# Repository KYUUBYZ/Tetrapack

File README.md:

# Tetrapack

<!--START_SECTION:BOM-TABLE-->
| Item | Qty | Supplier | Cost/item | Total Cost | link |
| --- | --- | --- | --- | --- | --- |
| Keyboard switches | 10 | Amazon | $7.28 | $7.28 | [Link](https://amzn.eu/d/03ocpfXx) |
| 20mm Plum handle | 1 | Aliexpress | $3.18 | $3.18 | [Link](https://it.aliexpress.com/item/1005009018396383.html?spm=a2g0o.detail.0.0.4a692ax52ax5IX&mp=1&pdp_npi=6%40dis%21EUR%21EUR+1.85%21EUR+1.85%21%21EUR+1.85%21%21%21%400b884b5817914834751998203e0efd%2112000047696154340%21ct%21IT%216215000935%21%212%210%21&_gl=1*12osb1n*_gcl_aw*R0NMLjE3OTA4ODQwMTEuQ2p3S0NBandpZmpWQmhCS0Vpd0FZeDRLOUV2cDdHVGR4MzdlMFFod2J2MVQyLXlndkJxdTJrSXZ4cHBPYnp2YVp2Y3BiVGtESldkVkJob0NEeDRRQXZEX0J3RQ..*_gcl_au*NzAxNTU5NzE5LjE3OTA4NzM0MTQ.*_ga*MjEzNDk1ODc5NjA4MTA1MC4xNzkwODczNDEzNDAz*_ga_VED1YSGNC7*czE3OTE0ODMzOTAkbzE5JGcxJHQxNzkxNDgzNDU1JGo2MCRsMCRoMA..&gatewayAdapt=glo2ita) |
| Display OLED 0,91 | 1 | Amazon | $9.98 | $9.98 | [Link](https://amzn.eu/d/0f2XTxEG) |
| Rp 2040 Zero | 1 | Amazon | $9.98 | $9.98 | [Link](https://amzn.eu/d/0fHYzSj0) |
| Estimated total shipping | 1 |  |  | $3 |  |
<!--END_SECTION:BOM-TABLE-->

TETRAPACK is a 9 keys, high pulling rate macropad, it exists because people (like me) needs shortcuts to things like programs, aps or maybe even channels on discord, or just use it for geometry dash (what I will do) or OSU.

The simbols schematic:

The PCB schematic:

It's a high pulling rate (1000hz) macropad, it's this fast because it uses a certain USB-c propriety useful for projects like this, everything about it (the code) is in src/host

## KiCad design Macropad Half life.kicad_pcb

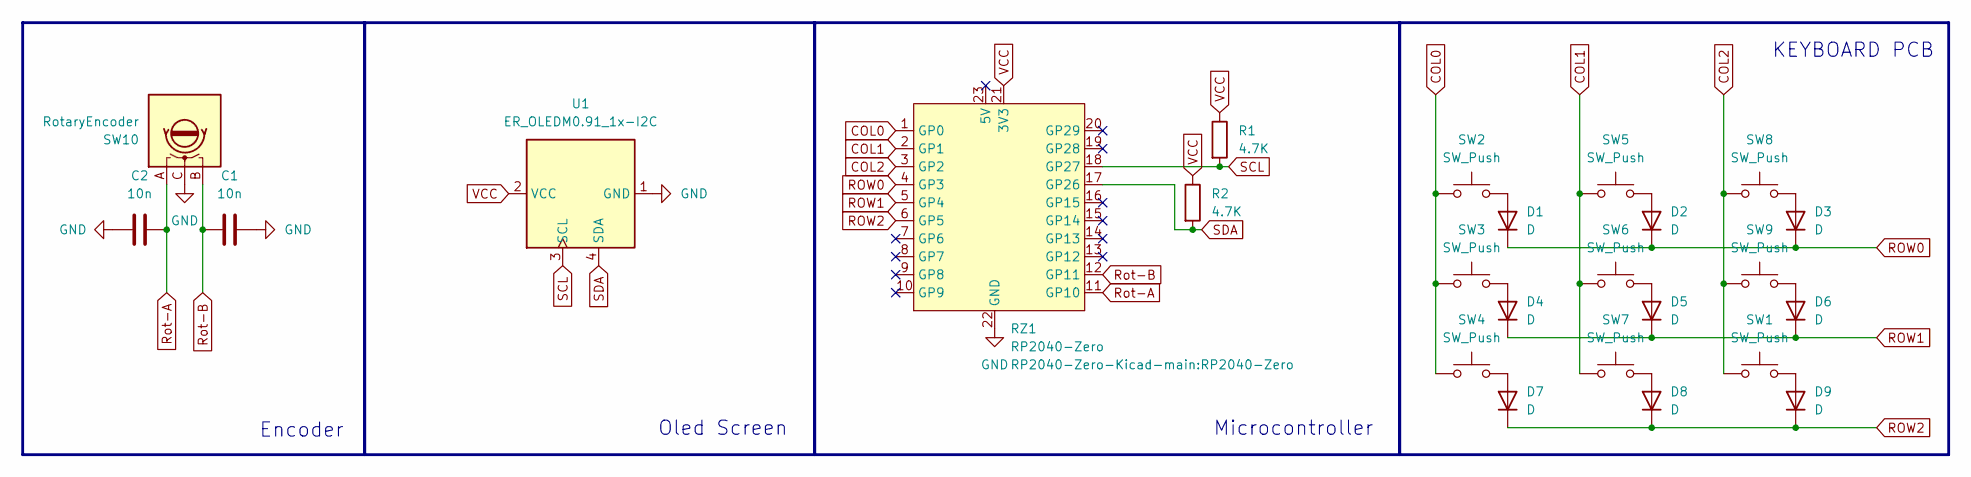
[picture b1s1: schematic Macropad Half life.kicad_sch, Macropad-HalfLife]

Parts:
C1, C2: 10n; C_0805_2012Metric_Pad1.18x1.45mm_HandSolder
D1, D2, D3, D4, D5, D6, D7, D8, D9: D; D_DO-41_SOD81_P10.16mm_Horizontal
R1, R2: 4.7K; R_0805_2012Metric_Pad1.20x1.40mm_HandSolder
RZ1: RP2040-Zero
SW1, SW2, SW3, SW4, SW5, SW6, SW7, SW8, SW9: SW_Push; SW_Cherry_MX_1.25u_PCB
SW10: RotaryEncoder; RotaryEncoder_Alps_EC12E_Vertical_H20mm
U1: ER_OLEDM0.91_1x-I2C

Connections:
COL0: RZ1.1 (GP0), SW2.1, SW3.1, SW4.1
COL1: RZ1.2 (GP1), SW5.1, SW6.1, SW7.1
COL2: RZ1.3 (GP2), SW1.1, SW8.1, SW9.1
GND: C1.2, C2.1, RZ1.22 (GND), SW10.C, U1.1 (GND)
unnamed: D1.2 (A), SW2.2
unnamed: D2.2 (A), SW5.2
unnamed: D3.2 (A), SW8.2
unnamed: D4.2 (A), SW3.2
unnamed: D5.2 (A), SW6.2
unnamed: D6.2 (A), SW9.2
unnamed: D7.2 (A), SW4.2
unnamed: D8.2 (A), SW7.2
unnamed: D9.2 (A), SW1.2
ROW0: D1.1 (K), D2.1 (K), D3.1 (K), RZ1.4 (GP3)
ROW1: D4.1 (K), D5.1 (K), D6.1 (K), RZ1.5 (GP4)
ROW2: D7.1 (K), D8.1 (K), D9.1 (K), RZ1.6 (GP5)
Rot-A: C2.2, RZ1.11 (GP10), SW10.A
Rot-B: C1.1, RZ1.12 (GP11), SW10.B
SCL: R1.2, RZ1.18 (GP27), U1.3 (SCL)
SDA: R2.2, RZ1.17 (GP26), U1.4 (SDA)
VCC: R1.1, R2.1, RZ1.21 (3V3), U1.2 (VCC)

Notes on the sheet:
Oled Screen
Microcontroller
KEYBOARD PCB
Encoder

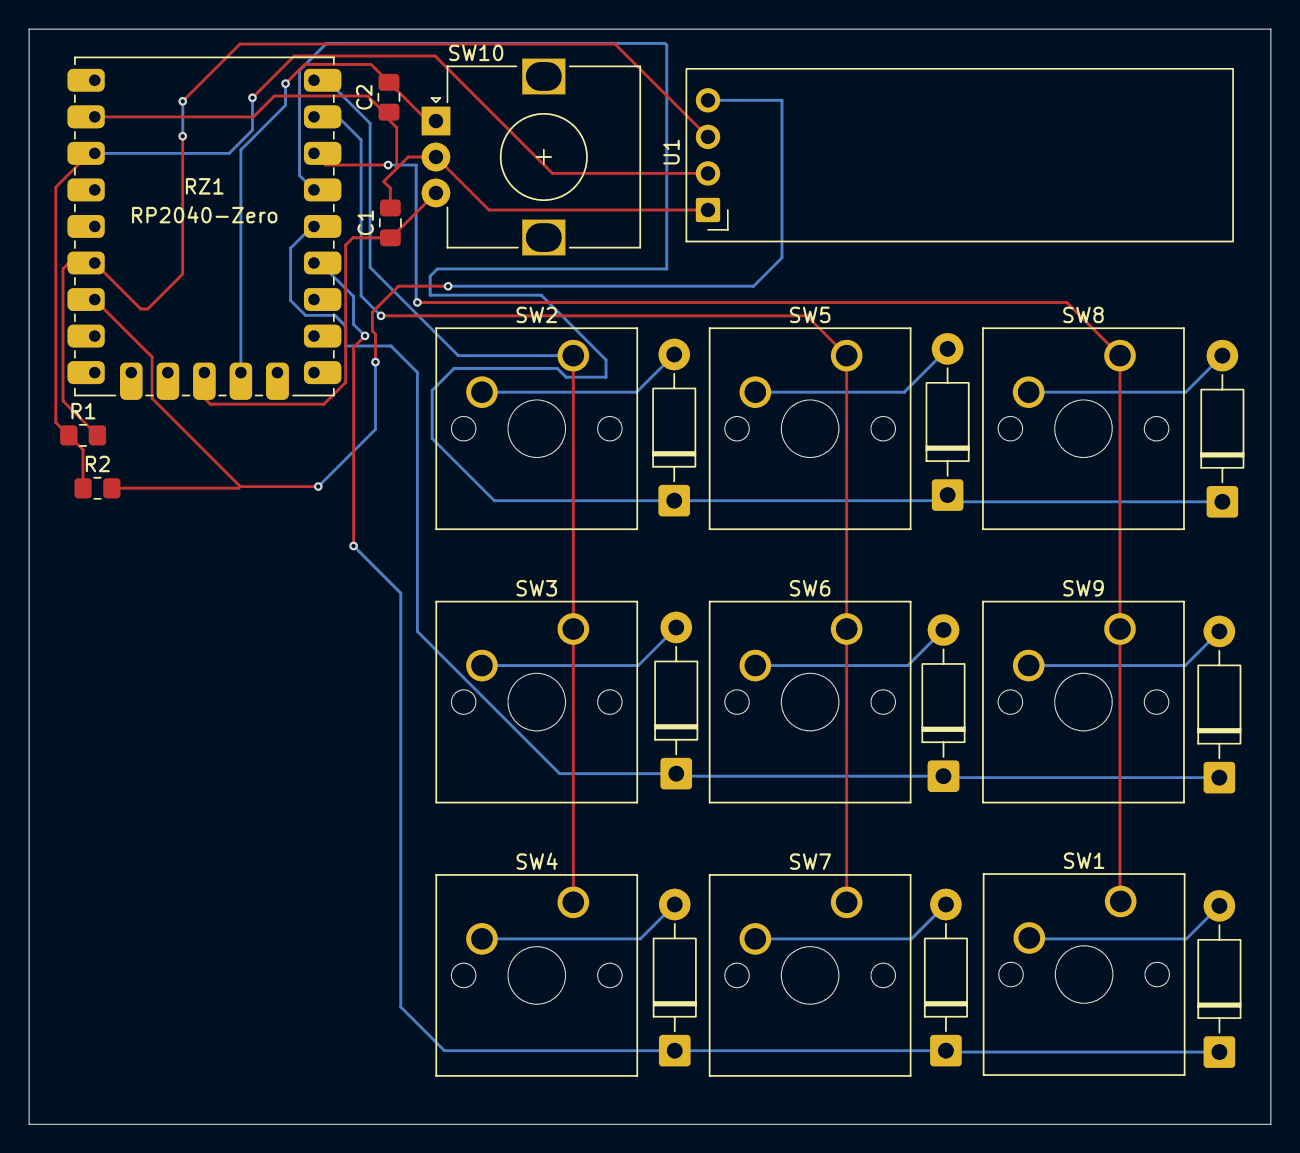
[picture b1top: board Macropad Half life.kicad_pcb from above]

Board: 2 copper layers, 86.3 x 76.1 mm, 25 parts (0 on the bottom side), 21 nets.
